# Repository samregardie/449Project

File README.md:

# 18-449 Project

Firmware for the STM32 Nucleo-F401RE (Zephyr) and the Raspberry Pi cockpit.

- `lab3/`: Lab 3 apps (`stm32-front`, `stm32-rear`, `pi/proxy_receiver`); pins in [`lab3/pins.md`](lab3/pins.md)
- `lab2/stm32/`: Lab 2 Zephyr app
- `setup449`: shell setup script

## Lab 3

### STM32 nodes

In every new shell, from `449Project/`:

```sh
source ./setup449
```

Then, from any folder:

```sh
west build-front     # N2, steering
west flash-front
west build-rear      # N3, drivetrain
west flash-rear
```

Add `-p` for a clean rebuild (`west build-front -p`). With both boards plugged in, add the board's serial number: `west flash-front --dev-id <serial>` (find it with `STM32_Programmer_CLI -l st-link`), or plug in one board at a time.

### Raspberry Pi

```sh
cd lab3/pi/proxy_receiver
sudo ./run.sh
```

It sets up both buses, builds and starts. Enter sends one out-of-range CTRL (bad-input test). Ctrl+C stops it. Watch the buses with `candump -c -t d any`.

## Lab 2

From `449Project/`:

```sh
west build -p always -b nucleo_f401re lab2/stm32   # full rebuild
west flash
west debugserver                                   # terminal 1
west debug                                         # terminal 2
```

For debugging, build with optimizations off:

```sh
west build -p always -b nucleo_f401re lab2/stm32 -- -DCONFIG_DEBUG_OPTIMIZATIONS=y -DCONFIG_DEBUG_THREAD_INFO=y
```

## Zephyr setup (one time)

This repo sits inside a west workspace:

```
zephyrproject/     ← west workspace (not tracked): .venv/ .west/ zephyr/ modules/
└── 449Project/           ← this repo
```

1. Follow the [Zephyr getting-started guide](https://docs.zephyrproject.org/latest/develop/getting_started/index.html) to install the host dependencies and the Zephyr SDK.
2. Install [STM32CubeProgrammer](https://www.st.com/en/development-tools/stm32cubeprog.html) (for `west flash`) and OpenOCD (for `west debug`; on macOS run `brew install openocd`).
3. Create the workspace and clone this repo into it:
   ```sh
   mkdir zephyrproject && cd zephyrproject
   python3 -m venv .venv
   source .venv/bin/activate
   pip install west
   west init -m https://github.com/zephyrproject-rtos/zephyr .
   west update
   west packages pip --install
   git clone <this-repo-url> 449Project
   ```
4. Check it works: the green LED (LD2) should blink.
   ```sh
   source ./setup449
   west build -p always -b nucleo_f401re ../zephyr/samples/basic/blinky
   west flash
   ```

`setup449` must be sourced, not executed. It activates the west venv and the Zephyr environment, and adds the Lab 3 shortcuts.

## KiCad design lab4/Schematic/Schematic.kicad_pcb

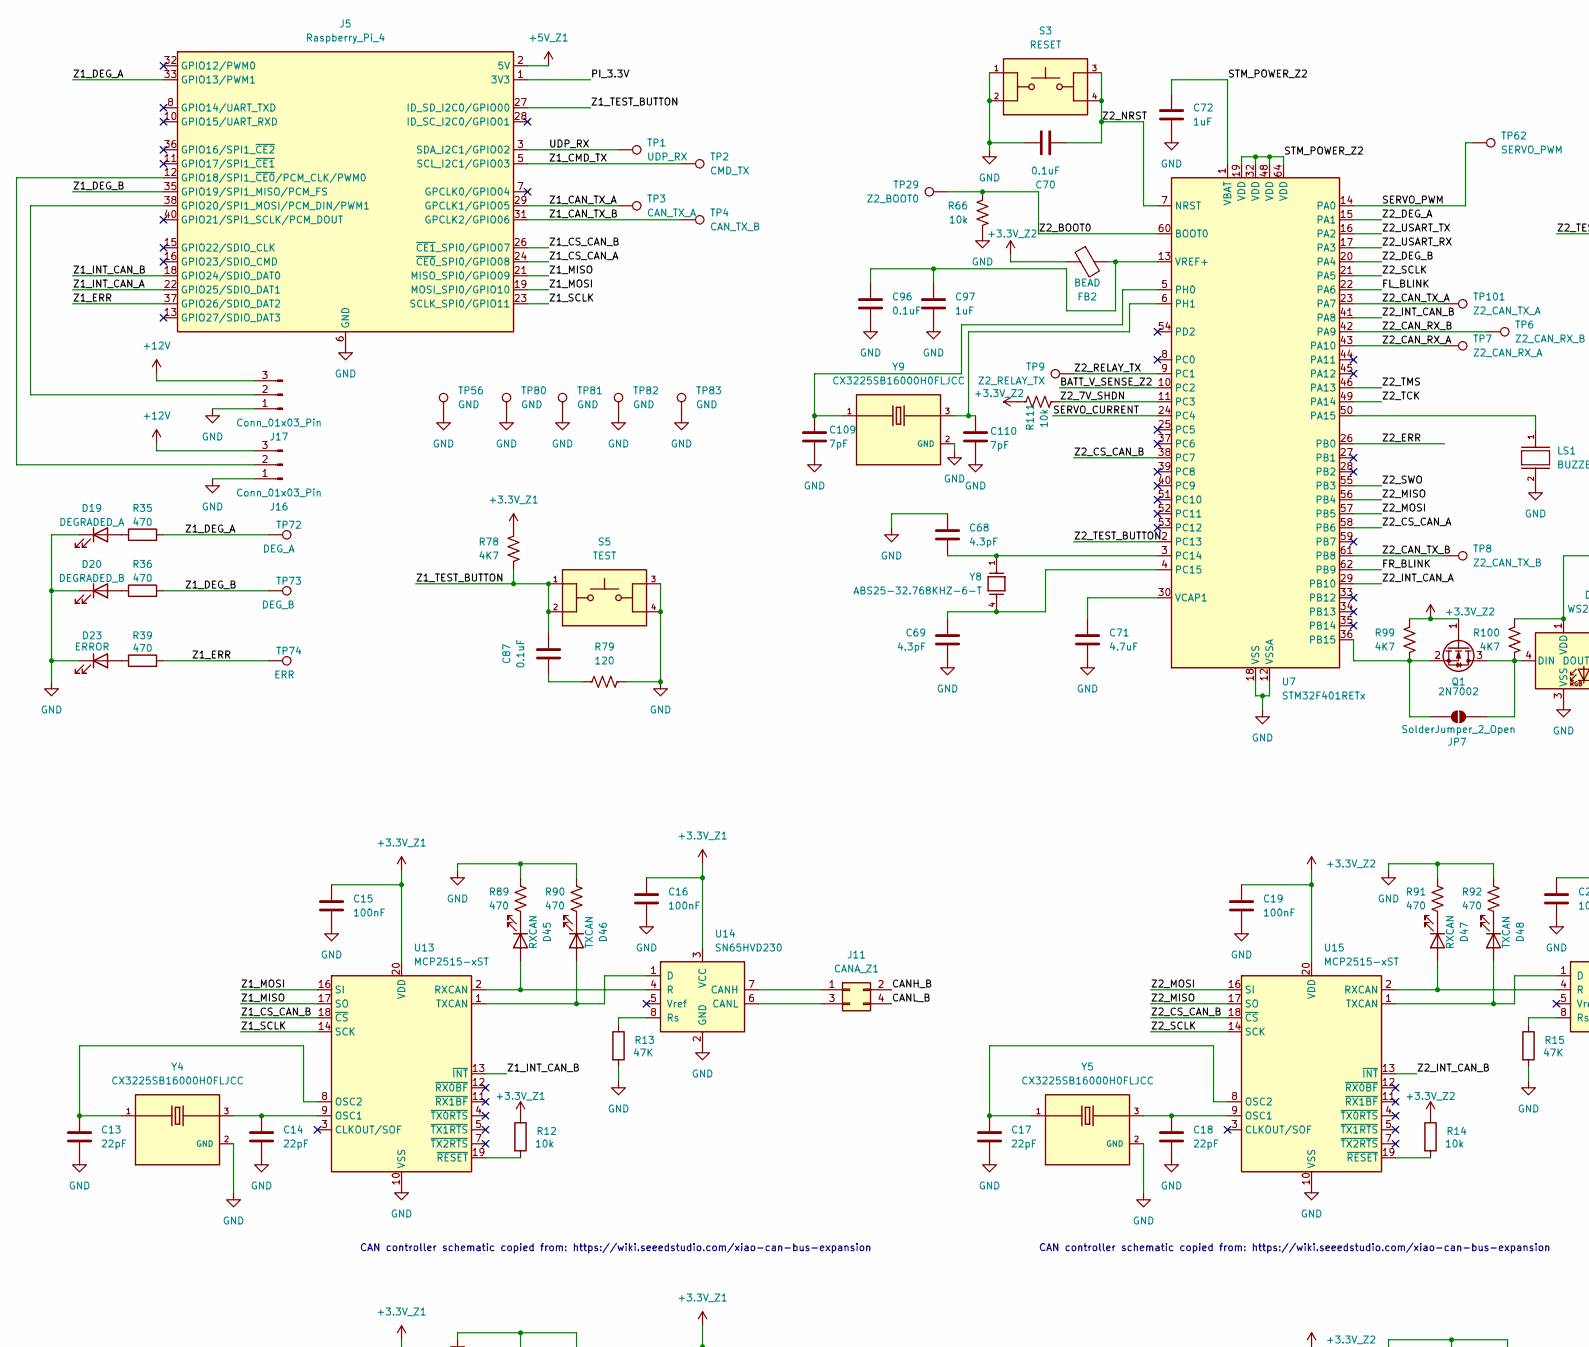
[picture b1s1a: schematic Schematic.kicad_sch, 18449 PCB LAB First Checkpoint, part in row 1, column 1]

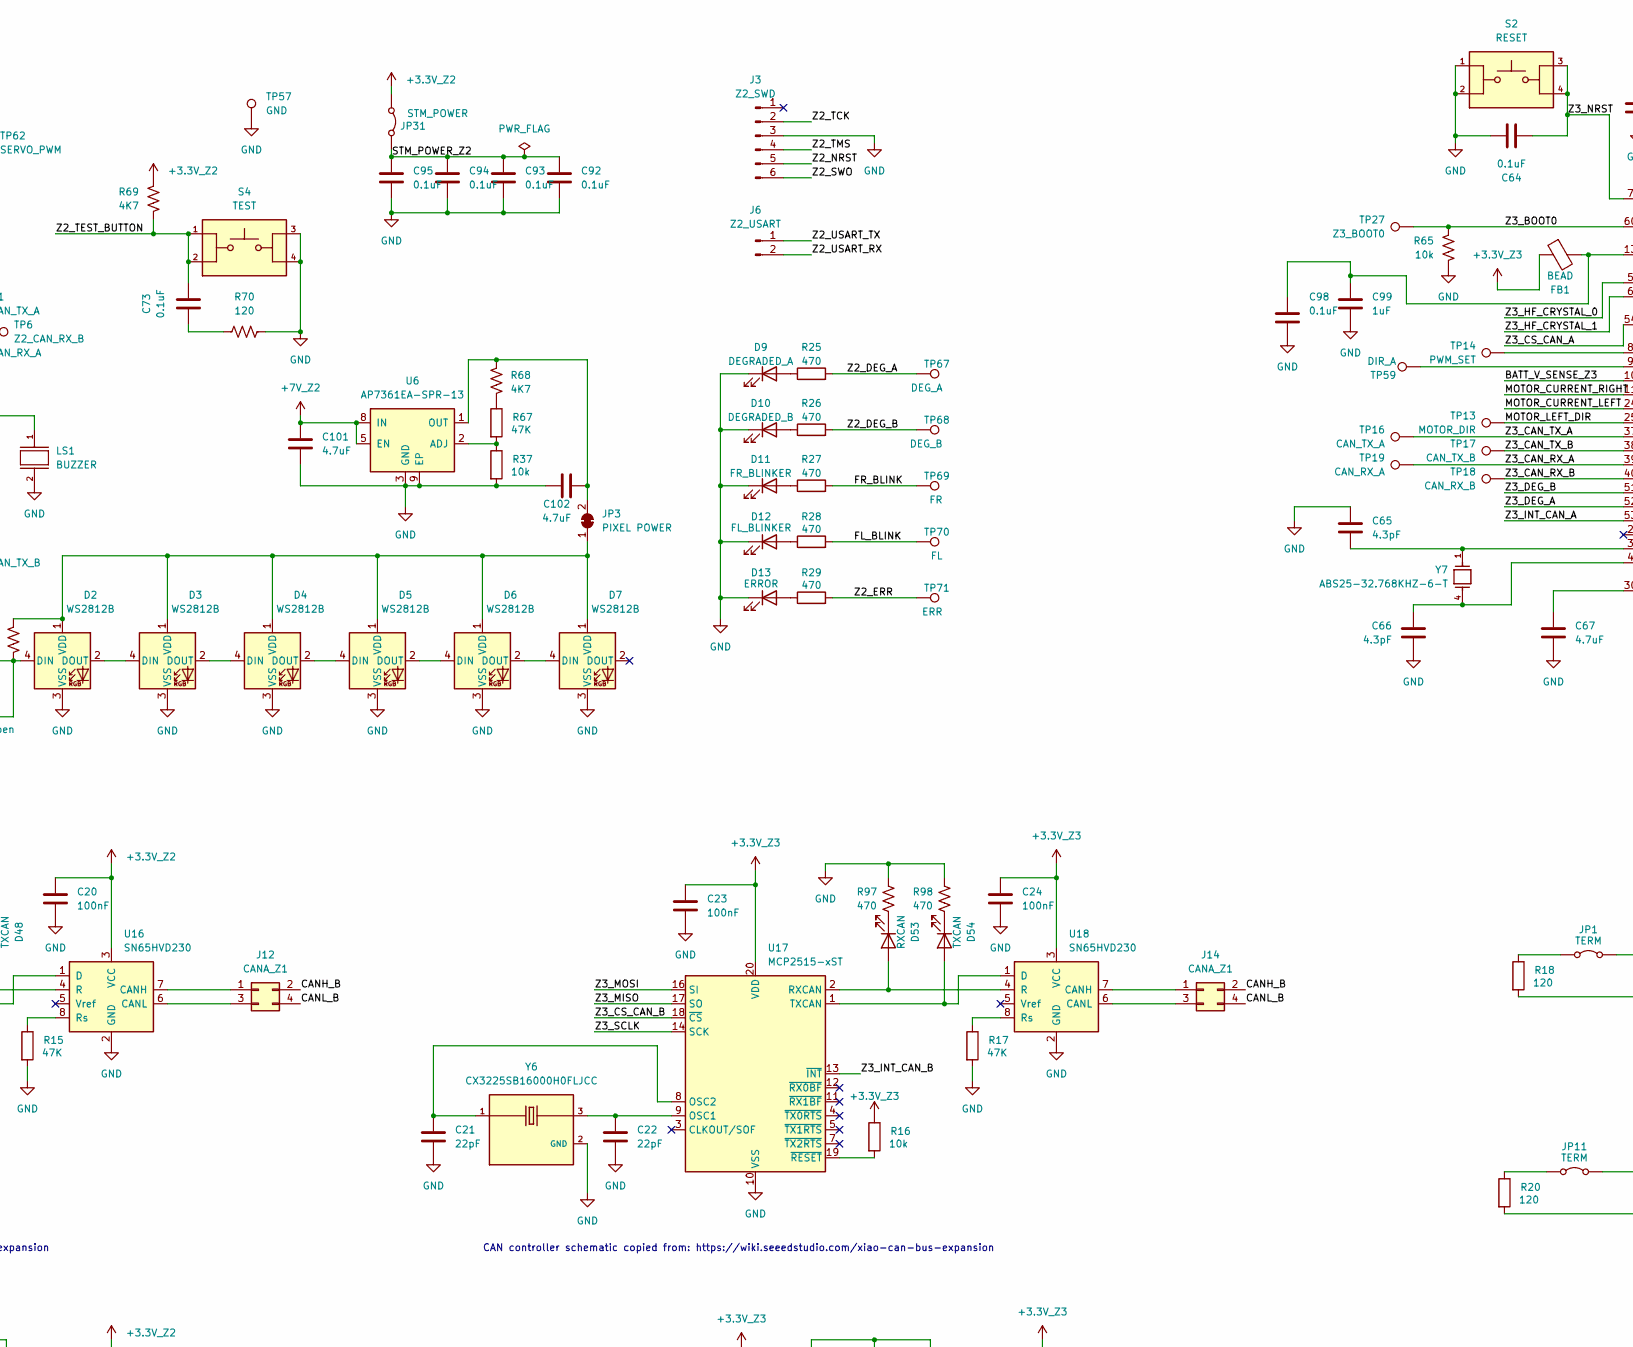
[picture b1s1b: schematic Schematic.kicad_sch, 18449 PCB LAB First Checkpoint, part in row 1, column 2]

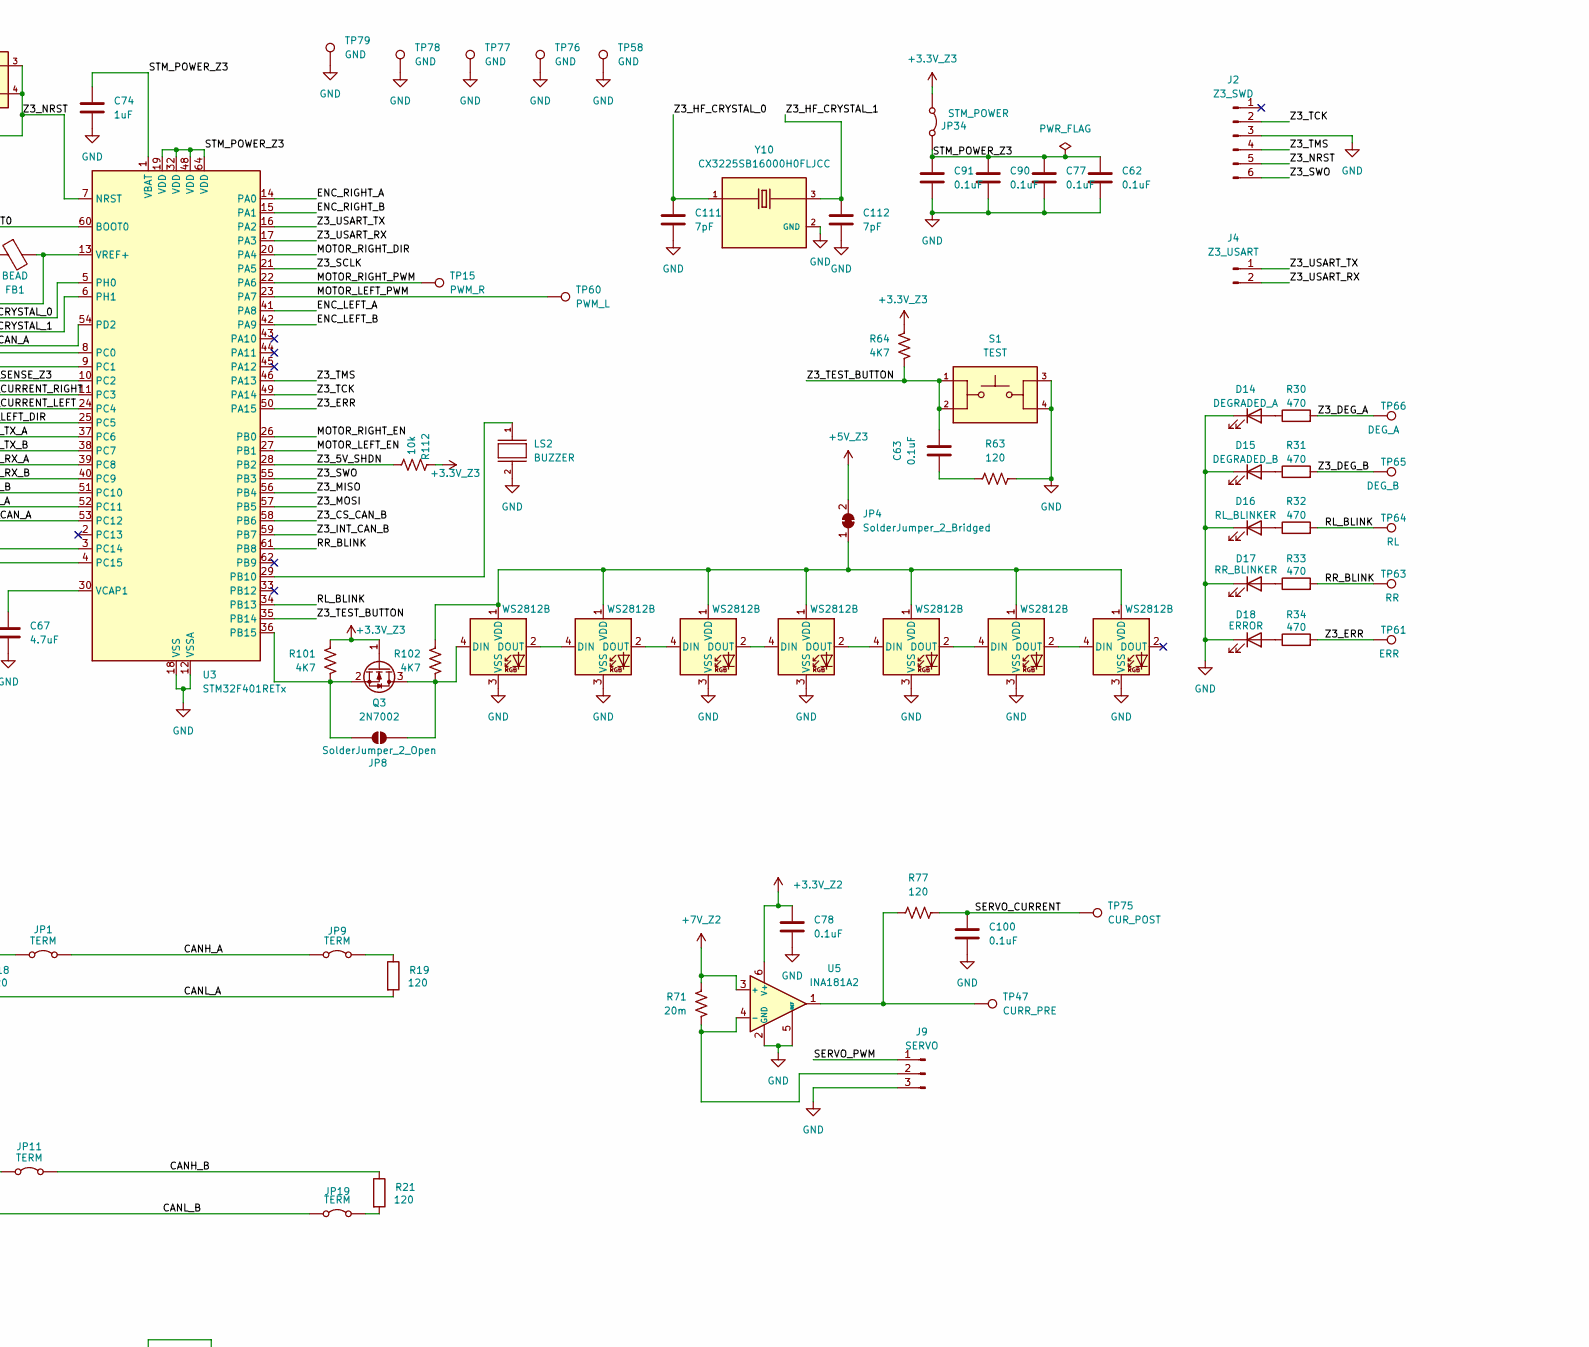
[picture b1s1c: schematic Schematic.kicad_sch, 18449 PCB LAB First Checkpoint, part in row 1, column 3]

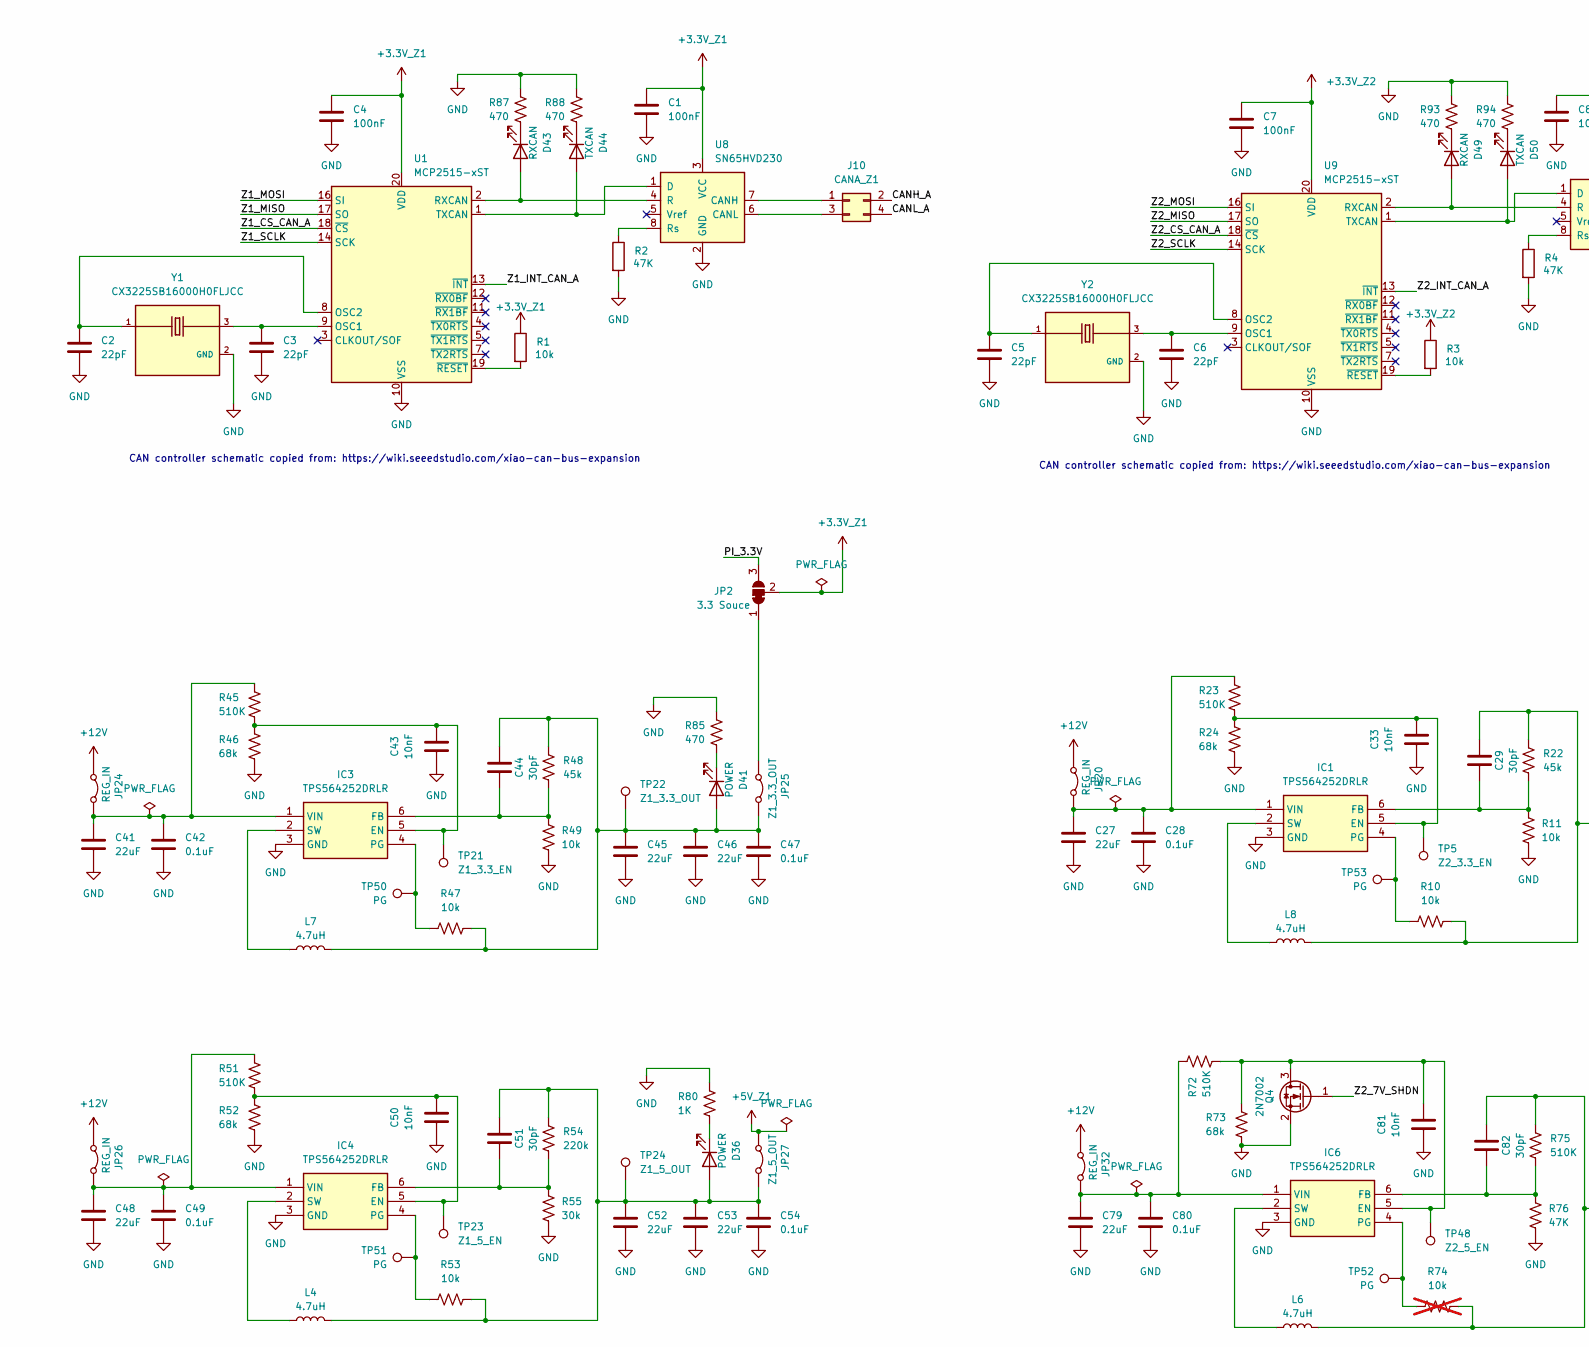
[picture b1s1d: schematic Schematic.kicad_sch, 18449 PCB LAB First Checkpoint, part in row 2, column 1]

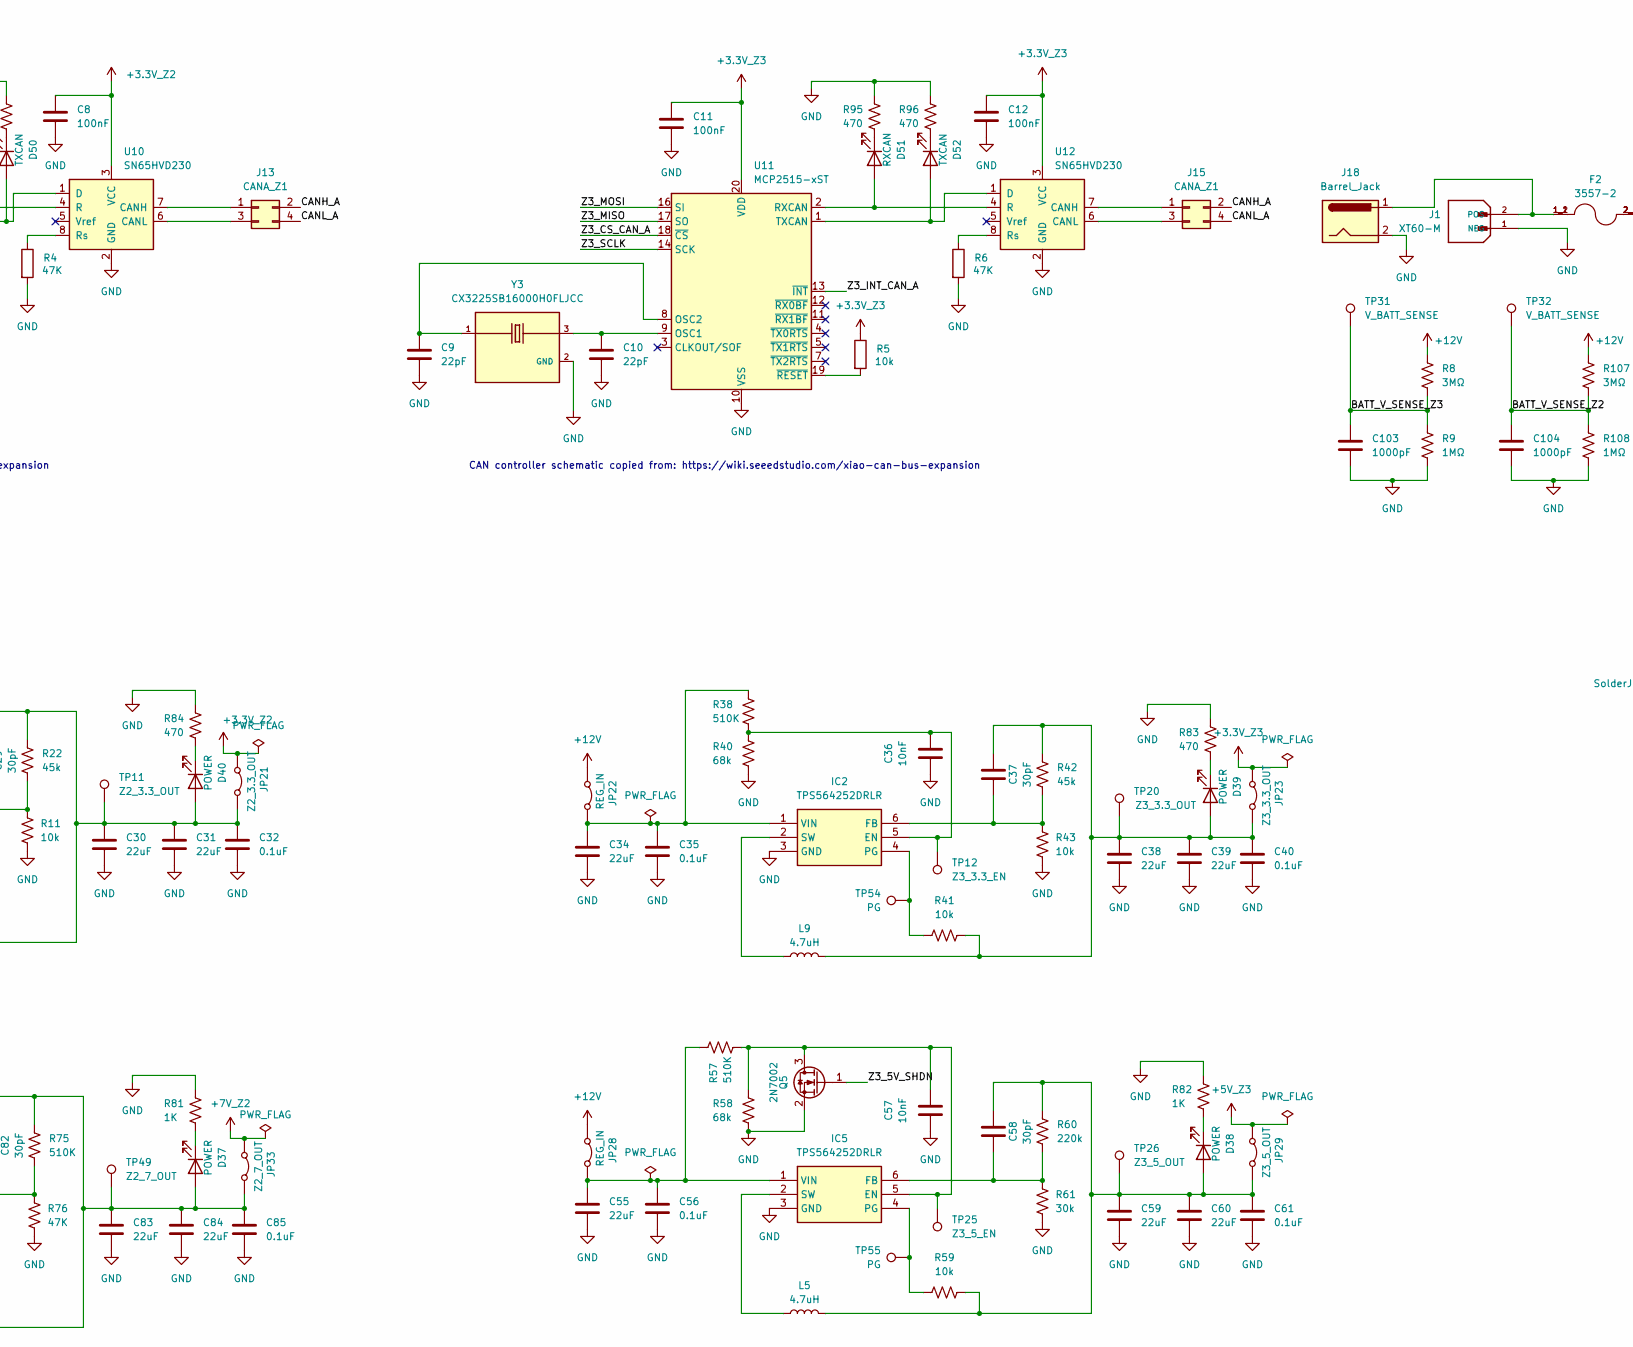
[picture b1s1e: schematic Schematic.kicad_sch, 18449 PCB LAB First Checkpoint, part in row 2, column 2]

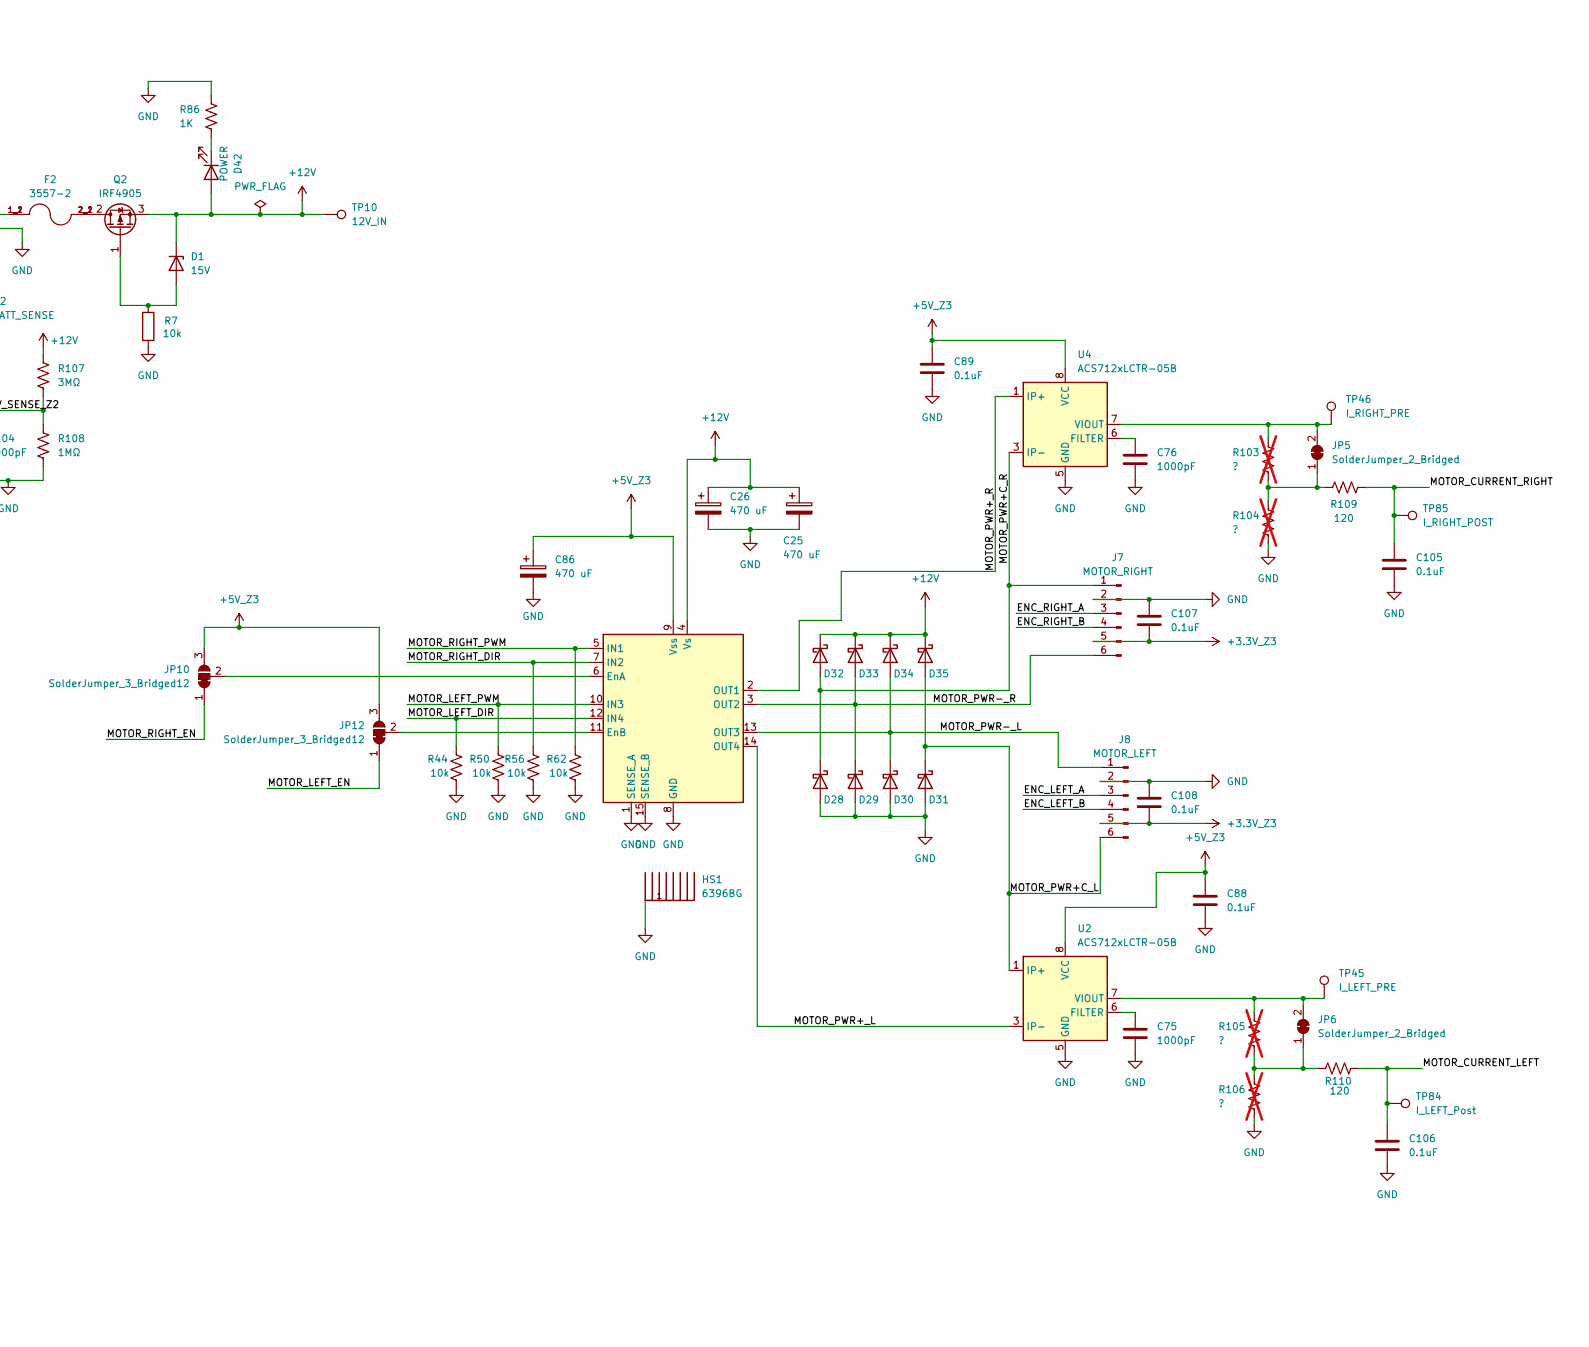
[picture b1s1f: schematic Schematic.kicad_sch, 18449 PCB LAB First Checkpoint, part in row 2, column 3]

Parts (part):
C1, C4, C7, C8, C11, C12, C15, C16, C19, C20, C23, C24: 100nF; C_0603_1608Metric; Manufacturer_Part_Number KGM15AR71C104KT
C2, C3, C5, C6, C9, C10, C13, C14, C17, C18, C21, C22: 22pF; C_0603_1608Metric; Manufacturer_Part_Number C0603C220J1GACTU
C25, C26, C86: 470 uF; CP_Elec_8x11.9_A768; Manufacturer_Part_Number A768KS477M1CLAE017
C27, C30, C31, C34, C38, C39, C41, C45, C46, C48, C52, C53, C55, C59, C60, C79, C83, C84: 22uF; C_0805_2012Metric; Manufacturer_Part_Number GRM219R61C226ME15L
C28, C32, C35, C40, C42, C47, C49, C54, C56, C61, C62, C63, C64, C70, C73, C77, C78, C80, C85, C87, C88, C89, C90, C91, C92, C93, C94, C95, C96, C98, C100, C105, C106, C107, C108: 0.1uF; C_0603_1608Metric; Manufacturer_Part_Number KGM15AR71C104KT
C29, C37, C44, C51, C58, C82: 30pF; C_0603_1608Metric; Manufacturer_Part_Number GRM1885C1H300JA01D
C33, C36, C43, C50, C57, C81: 10nF; C_0603_1608Metric; Manufacturer_Part_Number CC0603KRX7R9BB103
C65, C66, C68, C69: 4.3pF; C_0603_1608Metric; Manufacturer_Part_Number CC0603CRNPO9BN4R3
C67, C71, C101, C102: 4.7uF; C_0805_2012Metric; Manufacturer_Part_Number GRM21BR71C475KE51L
C72, C74, C97, C99: 1uF; C_0603_1608Metric; Manufacturer_Part_Number EMK107B7105KA-T
C75, C76, C103, C104: 1000pF; C_0603_1608Metric; Manufacturer_Part_Number GCM1885C2A102FA16D
C109, C110, C111, C112: 7pF; C_0603_1608Metric; Manufacturer_Part_Number CL10C070CB8NNNC
D1: 15V; D_SOD-123; Manufacturer_Part_Number BZT52C15
D2, D3, D4, D5, D6, D7, D8, D21, D22, D24, D25, D26, D27: WS2812B; LED_WS2812B_PLCC4_5.0x5.0mm_P3.2mm; Manufacturer_Part_Number 16347
D9, D14, D19: DEGRADED_A; LED_0603_1608Metric; Manufacturer_Part_Number LTST-C190KSKT
D10, D15, D20: DEGRADED_B; LED_0603_1608Metric; Manufacturer_Part_Number LTST-C190KSKT
D11: FR_BLINKER; LED_D3.0mm; Manufacturer_Part_Number 151031YS06000
D12: FL_BLINKER; LED_D3.0mm; Manufacturer_Part_Number 151031YS06000
D13, D18, D23: ERROR; LED_0603_1608Metric; Manufacturer_Part_Number LTST-C190KRKT
D16: RL_BLINKER; LED_D3.0mm; Manufacturer_Part_Number 151031YS06000
D17: RR_BLINKER; LED_D3.0mm; Manufacturer_Part_Number 151031YS06000
D28, D29, D30, D31, D32, D33, D34, D35: D_Schottky; D_SMB; Manufacturer_Part_Number SK520B
D36, D37, D38, D39, D40, D41, D42: POWER; LED_0603_1608Metric; Manufacturer_Part_Number LTST-C190GKT
D43, D45, D47, D49, D51, D53: RXCAN; LED_0603_1608Metric; Manufacturer_Part_Number LTST-C190GKT
D44, D46, D48, D50, D52, D54: TXCAN; LED_0603_1608Metric; Manufacturer_Part_Number LTST-C190GKT
F2: 3557-2; FUSE_3557-2; PARTREV D
FB1, FB2: BEAD; L_0603_1608Metric; Manufacturer_Part_Number 742863160
HS1: 6396BG; HSINK_6396BG; Manufacturer_Part_Number 6396BG
IC1, IC2, IC3, IC4, IC5, IC6: TPS564252DRLR; SOT50P160X60-6N; Mouser Part Number 595-TPS564252DRLR
J1: XT60-M; AMASS_XT60-M_1x02_P7.20mm_Vertical; PARTREV V1.2
J2: Z3_SWD; PinHeader_1x06_P2.54mm_Vertical
J3: Z2_SWD; PinHeader_1x06_P2.54mm_Vertical
J4: Z3_USART; PinHeader_1x02_P2.54mm_Vertical
J5: Raspberry_Pi_4; PinHeader_2x20_P2.54mm_Vertical
J6: Z2_USART; PinHeader_1x02_P2.54mm_Vertical
J7: MOTOR_RIGHT; JST_PH_B6B-PH-SM4-TB_1x06-1MP_P2.00mm_Vertical; Manufacturer_Part_Number B6B-PH-SM4-TB
J8: MOTOR_LEFT; JST_PH_B6B-PH-SM4-TB_1x06-1MP_P2.00mm_Vertical; Manufacturer_Part_Number B6B-PH-SM4-TB
J9: SERVO; PinHeader_1x03_P2.54mm_Vertical
J10, J11, J12, J13, J14, J15: CANA_Z1; PinHeader_2x02_P2.54mm_Vertical
J16, J17: Conn_01x03_Pin; PinHeader_1x03_P2.54mm_Vertical
J18: Barrel_Jack; BarrelJack_Horizontal; Manufacturer_Part_Number PJ-002A
JP1, JP9, JP11, JP19: TERM; PinHeader_1x02_P2.54mm_Vertical
JP2: 3.3 Souce; SolderJumper-3_P1.3mm_Bridged12_RoundedPad1.0x1.5mm_NumberL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
JP3: PIXEL POWER; SolderJumper-2_P1.3mm_Bridged_RoundedPad1.0x1.5mm
JP4, JP5, JP6: SolderJumper_2_Bridged; SolderJumper-2_P1.3mm_Bridged_RoundedPad1.0x1.5mm
JP7, JP8: SolderJumper_2_Open; SolderJumper-2_P1.3mm_Open_RoundedPad1.0x1.5mm
JP10, JP12: SolderJumper_3_Bridged12; SolderJumper-3_P1.3mm_Bridged12_RoundedPad1.0x1.5mm_NumberL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
JP20, JP22, JP24, JP26, JP28, JP32: REG_IN; PinHeader_1x02_P2.54mm_Vertical
JP21: Z2_3.3_OUT; PinHeader_1x02_P2.54mm_Vertical
JP23: Z3_3.3_OUT; PinHeader_1x02_P2.54mm_Vertical
JP25: Z1_3.3_OUT; PinHeader_1x02_P2.54mm_Vertical
JP27: Z1_5_OUT; PinHeader_1x02_P2.54mm_Vertical
JP29: Z3_5_OUT; PinHeader_1x02_P2.54mm_Vertical
JP31, JP34: STM_POWER; PinHeader_1x02_P2.54mm_Vertical
JP33: Z2_7_OUT; PinHeader_1x02_P2.54mm_Vertical
L4, L5, L6, L7, L8, L9: 4.7uH; L_Eaton_SDCHA1V80; Manufacturer_Part_Number SDCHA1V8040-4R7-R
LS1, LS2: BUZZER; XDCR_PS1240P02BT; Manufacturer_Part_Number PS1240P02BT
Q1, Q3, Q4, Q5: 2N7002; SOT-23; Manufacturer_Part_Number 2N7002LT1G
Q2: IRF4905; TO-220-3_Horizontal_TabDown; Manufacturer_Part_Number IRF4905PBF
R1, R3, R5, R7, R10, R11, R12, R14, R16, R37, R41, R43, R44, R47, R49, R50, R53, R56, R59, R62, R65, R66, R111, R112: 10k; R_0603_1608Metric; Manufacturer_Part_Number CRCW060310K0FKEA
R2, R4, R6, R13, R15, R17, R67, R76: 47K; R_0603_1608Metric; Manufacturer_Part_Number RC0603FR-0747KL
R8, R107: 3MΩ; R_0603_1608Metric; Manufacturer_Part_Number RMCF0603FT3M00
R9, R108: 1MΩ; R_0603_1608Metric; Manufacturer_Part_Number RC0603FR-071ML
R18, R19, R20, R21, R63, R70, R77, R79, R109, R110: 120; R_0603_1608Metric; Manufacturer_Part_Number RC0603FR-07120RL
R22, R42, R48: 45k; R_0603_1608Metric; Manufacturer_Part_Number RC0603FR-0745K3L
R23, R38, R45, R51, R57, R72, R75: 510K; R_0603_1608Metric; Manufacturer_Part_Number CRCW0603510KFKEAC
R24, R40, R46, R52, R58, R73: 68k; R_0603_1608Metric; Manufacturer_Part_Number RC0603FR-0768KL
R25, R26, R27, R28, R29, R30, R31, R32, R33, R34, R35, R36, R39, R83, R84, R85, R87, R88, R89, R90, R91, R92, R93, R94, R95, R96, R97, R98: 470; R_0603_1608Metric; Manufacturer_Part_Number RC0603FR-07470RL
R54, R60: 220k; R_0603_1608Metric; Manufacturer_Part_Number RC0603FR-07220KL
R55, R61: 30k; R_0603_1608Metric; Manufacturer_Part_Number RC0603FR-0730KL
R64, R68, R69, R78, R99, R100, R101, R102: 4K7; R_0603_1608Metric; Manufacturer_Part_Number RC0603FR-074K7L
R71: 20m; R_1206_3216Metric; Manufacturer_Part_Number MCS1632R020FER
R74: 10k; R_0603_1608Metric; Manufacturer_Part_Number CRCW060310K0FKEA; not fitted
R80, R81, R82, R86: 1K; R_0603_1608Metric; Manufacturer_Part_Number ERJ-3EKF1001V
R103, R104, R105, R106: ?; R_0603_1608Metric; not fitted
S1, S4, S5: TEST; SW_SWT0210-045026GSA_REVA; PARTREV A
S2, S3: RESET; SW_SWT0210-045026GSA_REVA; PARTREV A
TP1: UDP_RX; TestPoint_Keystone_5015_Micro_Mini
TP2: CMD_TX; TestPoint_Keystone_5015_Micro_Mini
TP3, TP16: CAN_TX_A; TestPoint_Keystone_5015_Micro_Mini
TP4, TP17: CAN_TX_B; TestPoint_Keystone_5015_Micro_Mini
TP5: Z2_3.3_EN; TestPoint_Keystone_5015_Micro_Mini
TP6: Z2_CAN_RX_B; TestPoint_Keystone_5015_Micro_Mini
TP7: Z2_CAN_RX_A; TestPoint_Keystone_5015_Micro_Mini
TP8: Z2_CAN_TX_B; TestPoint_Keystone_5015_Micro_Mini
TP9: Z2_RELAY_TX; TestPoint_Keystone_5015_Micro_Mini
TP10: 12V_IN; TestPoint_Keystone_5015_Micro_Mini
TP11: Z2_3.3_OUT; TestPoint_Keystone_5015_Micro_Mini
TP12: Z3_3.3_EN; TestPoint_Keystone_5015_Micro_Mini
TP13: MOTOR_DIR; TestPoint_Keystone_5015_Micro_Mini
TP14: PWM_SET; TestPoint_Keystone_5015_Micro_Mini
TP15: PWM_R; TestPoint_Keystone_5015_Micro_Mini
TP18: CAN_RX_B; TestPoint_Keystone_5015_Micro_Mini
TP19: CAN_RX_A; TestPoint_Keystone_5015_Micro_Mini
TP20: Z3_3.3_OUT; TestPoint_Keystone_5015_Micro_Mini
TP21: Z1_3.3_EN; TestPoint_Keystone_5015_Micro_Mini
TP22: Z1_3.3_OUT; TestPoint_Keystone_5015_Micro_Mini
TP23: Z1_5_EN; TestPoint_Keystone_5015_Micro_Mini
TP24: Z1_5_OUT; TestPoint_Keystone_5015_Micro_Mini
TP25: Z3_5_EN; TestPoint_Keystone_5015_Micro_Mini
TP26: Z3_5_OUT; TestPoint_Keystone_5015_Micro_Mini
TP27: Z3_BOOT0; TestPoint_Keystone_5015_Micro_Mini
TP29: Z2_BOOT0; TestPoint_Keystone_5015_Micro_Mini
TP31, TP32: V_BATT_SENSE; TestPoint_Keystone_5015_Micro_Mini
TP45: I_LEFT_PRE; TestPoint_Keystone_5015_Micro_Mini
TP46: I_RIGHT_PRE; TestPoint_Keystone_5015_Micro_Mini
TP47: CURR_PRE; TestPoint_Keystone_5015_Micro_Mini
TP48: Z2_5_EN; TestPoint_Keystone_5015_Micro_Mini
TP49: Z2_7_OUT; TestPoint_Keystone_5015_Micro_Mini
TP50, TP51, TP52, TP53, TP54, TP55: PG; TestPoint_Keystone_5015_Micro_Mini
TP56, TP57, TP58, TP76, TP77, TP78, TP79, TP80, TP81, TP82, TP83: GND; TestPoint_Keystone_5015_Micro_Mini
TP59: DIR_A; TestPoint_Keystone_5015_Micro_Mini
TP60: PWM_L; TestPoint_Keystone_5015_Micro_Mini
TP61, TP71, TP74: ERR; TestPoint_Keystone_5015_Micro_Mini
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
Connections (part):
+3.3V_Z1: C1.1, C4.1, C15.1, C16.1, JP2.2 (C), R1.1, R12.1, R78.1, U1.20 (VDD), U8.3 (VCC), U13.20 (VDD), U14.3 (VCC)
+3.3V_Z2: C7.1, C8.1, C19.1, C20.1, C78.1, FB2.1, JP21.2 (B), JP31.2 (B), Q1.1 (G), R3.1, R14.1, R69.1, R99.1, R111.1, U5.6 (V+), U9.20 (VDD), U10.3 (VCC), U15.20 (VDD), U16.3 (VCC)
+3.3V_Z3: C11.1, C12.1, C23.1, C24.1, C107.2, C108.2, FB1.1, J7.5, J8.5, JP23.2 (B), JP34.2 (B), Q3.1 (G), R5.1, R16.1, R64.1, R101.1, R112.1, U11.20 (VDD), U12.3 (VCC), U17.20 (VDD), U18.3 (VCC)
+5V_Z1: J5.2 (5V), J5.4 (5V), JP27.2 (B)
+5V_Z3: C86.1, C88.1, C89.1, JP4.2 (B), JP10.3 (B), JP12.3 (B), JP29.2 (B), U2.8 (VCC), U4.8 (VCC), U20.9 (Vss)
+7V_Z2: C101.1, JP33.2 (B), R71.1, U5.3 (+), U6.5 (EN), U6.8 (IN)
+12V: C25.1, C26.1, D1.1 (K), D32.1 (K), D33.1 (K), D34.1 (K), D35.1 (K), D42.2 (A), J16.3, J17.3, JP20.2 (B), JP22.2 (B), JP24.2 (B), JP26.2 (B), JP28.2 (B), JP32.2 (B), Q2.3 (S), R8.1, R107.1, TP10.1 (1_1), U20.4 (Vs)
/BATT_V_SENSE_Z2: C104.1, R107.2, R108.1, TP32.1 (1_1), U7.10 (PC2)
/BATT_V_SENSE_Z3: C103.1, R8.2, R9.1, TP31.1 (1_1), U3.10 (PC2)
/CANH_A: J10.2, J13.2, J15.2, JP1.2 (B), JP9.1 (A)
/CANH_B: J11.2, J12.2, J14.2, JP11.2 (B), R21.1
/CANL_A: J10.4, J13.4, J15.4, R18.2, R19.2
/CANL_B: J11.4, J12.4, J14.4, JP19.1 (A), R20.2
/ENC_LEFT_A: J8.3, U3.41 (PA8)
/ENC_LEFT_B: J8.4, U3.42 (PA9)
/ENC_RIGHT_A: J7.3, U3.14 (PA0)
/ENC_RIGHT_B: J7.4, U3.15 (PA1)
/FL_BLINK: R28.2, TP70.1 (1_1), U7.22 (PA6)
/FR_BLINK: R27.2, TP69.1 (1_1), U7.62 (PB9)
/MOTOR_CURRENT_LEFT: C106.1, R110.2, TP84.1 (1_1), U3.24 (PC4)
/MOTOR_CURRENT_RIGHT: C105.1, R109.2, TP85.1 (1_1), U3.11 (PC3)
/MOTOR_LEFT_DIR: R44.1, TP13.1 (1_1), U3.25 (PC5), U20.12 (IN4)
/MOTOR_LEFT_EN: JP12.1 (A), U3.27 (PB1)
/MOTOR_LEFT_PWM: R50.1, TP60.1 (1_1), U3.23 (PA7), U20.10 (IN3)
/MOTOR_PWR+C_L: D31.1 (K), D35.2 (A), J8.6, U2.1 (IP+), U2.2 (IP+)
/MOTOR_PWR+C_R: D28.1 (K), D32.2 (A), J7.1, U4.3 (IP-), U4.4 (IP-)
/MOTOR_PWR+_L: U2.3 (IP-), U2.4 (IP-), U20.14 (OUT4)
/MOTOR_PWR+_R: U4.1 (IP+), U4.2 (IP+), U20.2 (OUT1)
/MOTOR_PWR-_L: D30.1 (K), D34.2 (A), J8.1, U20.13 (OUT3)
/MOTOR_PWR-_R: D29.1 (K), D33.2 (A), J7.6, U20.3 (OUT2)
/MOTOR_RIGHT_DIR: R56.1, U3.20 (PA4), U20.7 (IN2)
/MOTOR_RIGHT_EN: JP10.1 (A), U3.26 (PB0)
/MOTOR_RIGHT_PWM: R62.1, TP15.1 (1_1), U3.22 (PA6), U20.5 (IN1)
/PI_3.3V: J5.1 (3V3), J5.17 (3V3), JP2.3 (B)
/RL_BLINK: R32.2, TP64.1 (1_1), U3.34 (PB13)
/RR_BLINK: R33.2, TP63.1 (1_1), U3.61 (PB8)
/SERVO_CURRENT: C100.1, R77.2, TP75.1 (1_1), U7.24 (PC4)
/SERVO_PWM: J9.1, TP62.1 (1_1), U7.14 (PA0)
/STM_POWER_Z2: C72.1, C92.1, C93.1, C94.1, C95.1, JP31.1 (A), U7.1 (VBAT), U7.19 (VDD), U7.32 (VDD), U7.48 (VDD), U7.64 (VDD)
/STM_POWER_Z3: C62.1, C74.1, C77.1, C90.1, C91.1, JP34.1 (A), U3.1 (VBAT), U3.19 (VDD), U3.32 (VDD), U3.48 (VDD), U3.64 (VDD)
/UDP_RX: J5.3 (SDA_I2C1/GPIO02), TP1.1 (1_1)
/Z1_CAN_TX_A: J5.29 (GPCLK1/GPIO05), TP3.1 (1_1)
/Z1_CAN_TX_B: J5.31 (GPCLK2/GPIO06), TP4.1 (1_1)
/Z1_CMD_TX: J5.5 (SCL_I2C1/GPIO03), TP2.1 (1_1)
/Z1_CS_CAN_A: J5.24 (~CE0_SPI0/GPIO08), U1.18 (~CS)
/Z1_CS_CAN_B: J5.26 (~CE1_SPI0/GPIO07), U13.18 (~CS)
/Z1_DEG_A: J5.33 (GPIO13/PWM1), R35.2, TP72.1 (1_1)
/Z1_DEG_B: J5.35 (GPIO19/SPI1_MISO/PCM_FS), R36.2, TP73.1 (1_1)
/Z1_ERR: J5.37 (GPIO26/SDIO_DAT2), R39.2, TP74.1 (1_1)
/Z1_INT_CAN_A: J5.22 (GPIO25/SDIO_DAT1), U1.13 (~INT)
/Z1_INT_CAN_B: J5.18 (GPIO24/SDIO_DAT0), U13.13 (~INT)
/Z1_MISO: J5.21 (MISO_SPI0/GPIO09), U1.17 (SO), U13.17 (SO)
/Z1_MOSI: J5.19 (MOSI_SPI0/GPIO10), U1.16 (SI), U13.16 (SI)
/Z1_SCLK: J5.23 (SCLK_SPI0/GPIO11), U1.14 (SCK), U13.14 (SCK)
/Z1_TEST_BUTTON: C87.1, J5.27 (ID_SD_I2C0/GPIO00), R78.2, S5.1, S5.2
/Z2_7V_SHDN: Q4.1 (G), R111.2, U7.11 (PC3)
/Z2_BOOT0: R66.1, TP29.1 (1_1), U7.60 (BOOT0)
/Z2_CAN_RX_A: TP7.1 (1_1), U7.43 (PA10)
/Z2_CAN_RX_B: TP6.1 (1_1), U7.42 (PA9)
/Z2_CAN_TX_A: TP101.1 (1_1), U7.23 (PA7)
/Z2_CAN_TX_B: TP8.1 (1_1), U7.61 (PB8)
/Z2_CS_CAN_A: U7.58 (PB6), U9.18 (~CS)
/Z2_CS_CAN_B: U7.38 (PC7), U15.18 (~CS)
/Z2_DEG_A: R25.2, TP67.1 (1_1), U7.15 (PA1)
/Z2_DEG_B: R26.2, TP68.1 (1_1), U7.20 (PA4)
/Z2_ERR: R29.2, TP71.1 (1_1), U7.26 (PB0)
/Z2_INT_CAN_A: U7.29 (PB10), U9.13 (~INT)
/Z2_INT_CAN_B: U7.41 (PA8), U15.13 (~INT)
/Z2_MISO: U7.56 (PB4), U9.17 (SO), U15.17 (SO)
/Z2_MOSI: U7.57 (PB5), U9.16 (SI), U15.16 (SI)
/Z2_NRST: C70.2, J3.5, S3.3, S3.4, U7.7 (NRST)
/Z2_RELAY_TX: TP9.1 (1_1), U7.9 (PC1)
/Z2_SCLK: U7.21 (PA5), U9.14 (SCK), U15.14 (SCK)
/Z2_SWO: J3.6, U7.55 (PB3)
/Z2_TCK: J3.2, U7.49 (PA14)
/Z2_TEST_BUTTON: C73.1, R69.2, S4.1, S4.2, U7.2 (PC13)
/Z2_TMS: J3.4, U7.46 (PA13)
/Z2_USART_RX: J6.2, U7.17 (PA3)
/Z2_USART_TX: J6.1, U7.16 (PA2)
/Z3_5V_SHDN: Q5.1 (G), R112.2, U3.28 (PB2)
/Z3_BOOT0: R65.1, TP27.1 (1_1), U3.60 (BOOT0)
/Z3_CAN_RX_A: TP19.1 (1_1), U3.39 (PC8)
/Z3_CAN_RX_B: TP18.1 (1_1), U3.40 (PC9)
/Z3_CAN_TX_A: TP16.1 (1_1), U3.37 (PC6)
/Z3_CAN_TX_B: TP17.1 (1_1), U3.38 (PC7)
/Z3_CS_CAN_A: U3.54 (PD2), U11.18 (~CS)
/Z3_CS_CAN_B: U3.58 (PB6), U17.18 (~CS)
/Z3_DEG_A: R30.2, TP66.1 (1_1), U3.52 (PC11)
/Z3_DEG_B: R31.2, TP65.1 (1_1), U3.51 (PC10)
/Z3_ERR: R34.2, TP61.1 (1_1), U3.50 (PA15)
/Z3_HF_CRYSTAL_0: C111.1, U3.5 (PH0), Y10.1
/Z3_HF_CRYSTAL_1: C112.1, U3.6 (PH1), Y10.3
/Z3_INT_CAN_A: U3.53 (PC12), U11.13 (~INT)
/Z3_INT_CAN_B: U3.59 (PB7), U17.13 (~INT)
/Z3_MISO: U3.56 (PB4), U11.17 (SO), U17.17 (SO)
/Z3_MOSI: U3.57 (PB5), U11.16 (SI), U17.16 (SI)
/Z3_NRST: C64.2, J2.5, S2.3, S2.4, U3.7 (NRST)
/Z3_SCLK: U3.21 (PA5), U11.14 (SCK), U17.14 (SCK)
/Z3_SWO: J2.6, U3.55 (PB3)
/Z3_TCK: J2.2, U3.49 (PA14)
/Z3_TEST_BUTTON: C63.1, R64.2, S1.1, S1.2, U3.35 (PB14)
/Z3_TMS: J2.4, U3.46 (PA13)
/Z3_USART_RX: J4.2, U3.17 (PA3)
/Z3_USART_TX: J4.1, U3.16 (PA2)
GND: C1.2, C2.2, C3.2, C4.2, C5.2, C6.2, C7.2, C8.2, C9.2, C10.2, C11.2, C12.2, C13.2, C14.2, C15.2, C16.2, C17.2, C18.2, C19.2, C20.2, C21.2, C22.2, C23.2, C24.2, C25.2, C26.2, C27.2, C28.2, C30.2, C31.2, C32.2, C33.2, C34.2, C35.2, C36.2, C38.2, C39.2, C40.2, C41.2, C42.2, C43.2, C45.2, C46.2, C47.2, C48.2, C49.2, C50.2, C52.2, C53.2, C54.2, C55.2, C56.2, C57.2, C59.2, C60.2, C61.2, C62.2, C64.1, C65.1, C66.2, C67.2, C68.1, C69.2, C70.1, C71.2, C72.2, C74.2, C75.2, C76.2, C77.2, C78.2, C79.2, C80.2, C81.2, C83.2, C84.2, C85.2, C86.2, C88.2, C89.2, C90.2, C91.2, C92.2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; also elsewhere on the board
unnamed: C63.2, R63.1
unnamed: C73.2, R70.1
unnamed: C87.2, R79.1
unnamed: D1.2 (A), Q2.1 (G), R7.1
unnamed: D2.4 (DIN), JP7.1 (A), Q1.3 (D), R100.2
unnamed: D2.2 (DOUT), D3.4 (DIN)
unnamed: D2.1 (VDD), D3.1 (VDD), D4.1 (VDD), D5.1 (VDD), D6.1 (VDD), D7.1 (VDD), JP3.1 (A), R100.1
unnamed: D3.2 (DOUT), D4.4 (DIN)
unnamed: D4.2 (DOUT), D5.4 (DIN)
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
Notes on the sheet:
CAN controller schematic copied from: https://wiki.seeedstudio.com/xiao-can-bus-expansion

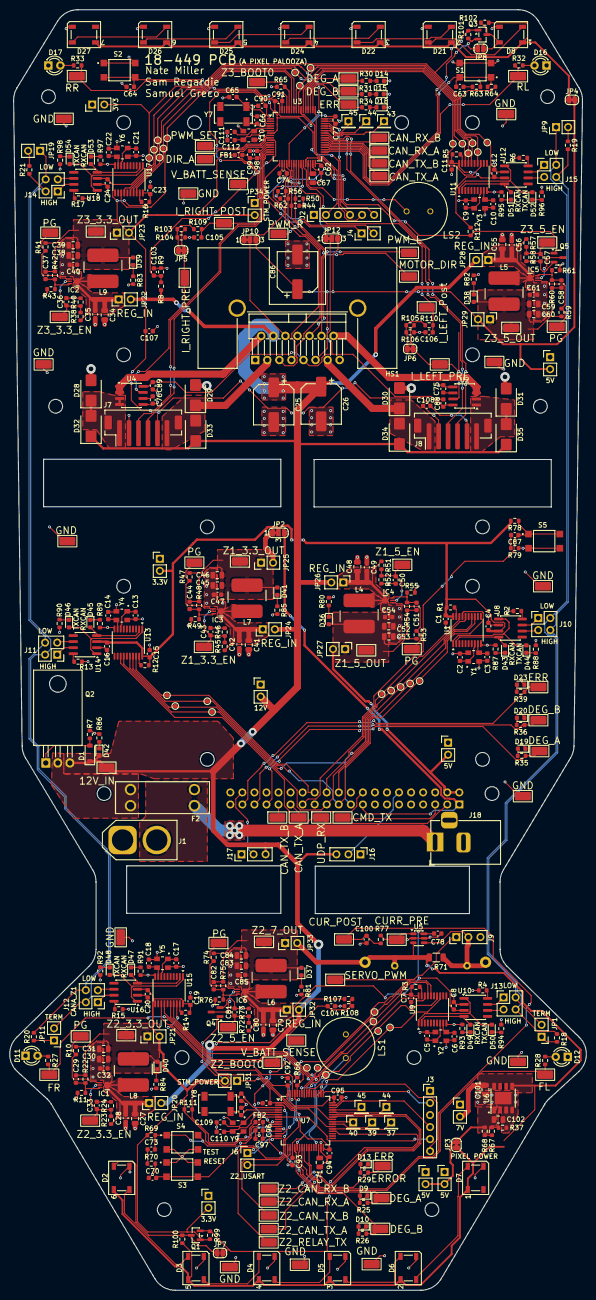
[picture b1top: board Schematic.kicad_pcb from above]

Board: 2 copper layers, 121.5 x 269.9 mm, 462 parts (1 on the bottom side), 278 nets.

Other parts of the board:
37, 39, 40, 43, 44, 44#2, 45, 45#2: PinHeader_1x01_P2.54mm_Vertical
TP57#2, TP57#3: GND; TestPoint_Keystone_5015_Micro_Mini

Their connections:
GND: TP57#2.1 (1_1), TP57#3.1 (1_1); also elsewhere on the board
